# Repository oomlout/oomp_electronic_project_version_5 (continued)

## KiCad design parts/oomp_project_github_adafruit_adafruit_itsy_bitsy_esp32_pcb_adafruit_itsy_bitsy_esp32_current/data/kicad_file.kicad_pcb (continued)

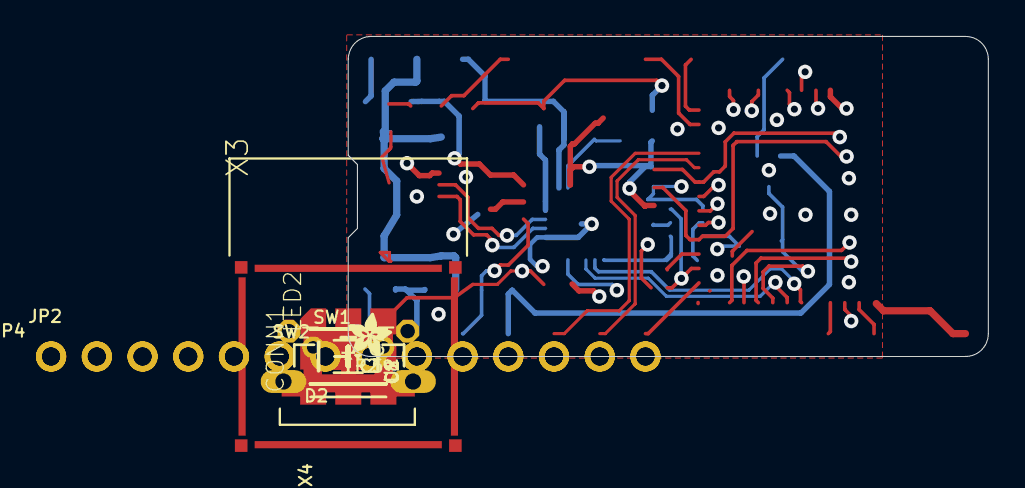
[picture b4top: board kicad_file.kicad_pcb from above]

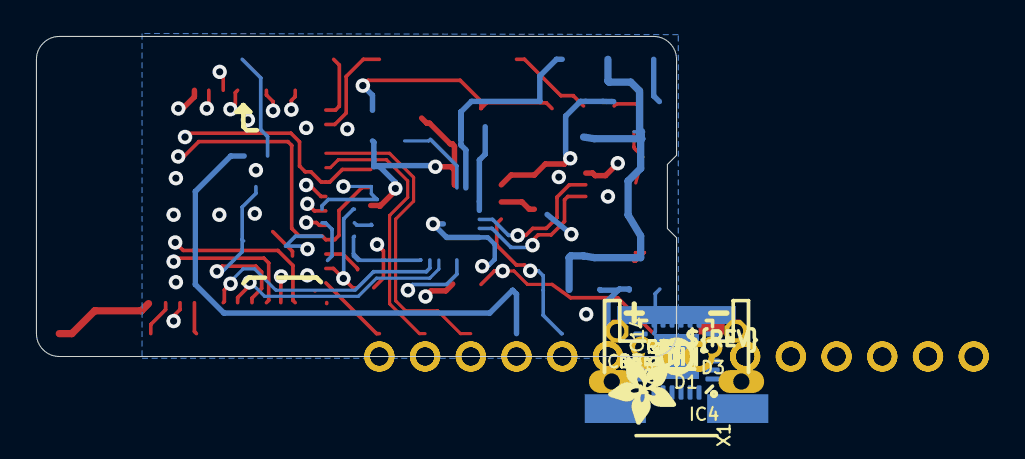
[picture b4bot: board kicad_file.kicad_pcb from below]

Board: 4 copper layers, 35.6 x 17.8 mm, 87 parts (48 on the bottom side), 42 nets.

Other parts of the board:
E$1: ADAFRUIT_2.5MM
E$2: ADAFRUIT_3.5MM
PLABEL0: PLABEL0
PLABEL1: PLABEL1
PLABEL2: PLABEL2
PLABEL3: PLABEL3
PLABEL4: PLABEL4
PLABEL5: PLABEL5
PLABEL6: PLABEL6
PLABEL7: PLABEL7
PLABEL8: PLABEL8
PLABEL9: PLABEL9
PLABEL10: PLABEL10
PLABEL11: PLABEL11
PLABEL12: PLABEL12
PLABEL13: PLABEL13
PLABEL14: PLABEL14
PLABEL15: PLABEL15
PLABEL16: PLABEL16
PLABEL17: PLABEL17
PLABEL18: PLABEL18
PLABEL19: PLABEL19
PLABEL20: PLABEL20
PLABEL21: PLABEL21
PLABEL22: PLABEL22
PLABEL23: PLABEL23
PLABEL24: PLABEL24
PLABEL25: PLABEL25
PLABEL26: PLABEL26
PLABEL27: PLABEL27
PLABEL28: PLABEL28
PLABEL29: PLABEL29
PLABEL30: PLABEL30
PLABEL31: PLABEL31
PLABEL32: PLABEL32
PLABEL33: PLABEL33
PLABEL34: PLABEL34
PLABEL35: PLABEL35
PLABEL36: PLABEL36
PLABEL37: PLABEL37
PLABEL38: PLABEL38
PLABEL39: PLABEL39
PLABEL40: PLABEL40
PLABEL41: PLABEL41
PLABEL42: PLABEL42
PLABEL43: PLABEL43
PLABEL44: PLABEL44
U$16: PCBFEAT-REV-040

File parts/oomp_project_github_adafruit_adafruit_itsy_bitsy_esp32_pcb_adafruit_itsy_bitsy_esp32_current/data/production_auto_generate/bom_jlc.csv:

Comment,Designator,Footprint,LCSC Part #
,"JP2,JP4",Adafruit ItsyBitsy ESP32-import-fps:1X14_ROUND70,C2905490
,E$1,Adafruit ItsyBitsy ESP32-import-fps:ADAFRUIT_2.5MM,
,E$2,Adafruit ItsyBitsy ESP32-import-fps:ADAFRUIT_3.5MM,
,U$16,Adafruit ItsyBitsy ESP32-import-fps:PCBFEAT-REV-040,
,PLABEL0,Adafruit ItsyBitsy ESP32-import-fps:PLABEL0,
,PLABEL1,Adafruit ItsyBitsy ESP32-import-fps:PLABEL1,
,PLABEL10,Adafruit ItsyBitsy ESP32-import-fps:PLABEL10,
,PLABEL11,Adafruit ItsyBitsy ESP32-import-fps:PLABEL11,
,PLABEL12,Adafruit ItsyBitsy ESP32-import-fps:PLABEL12,
,PLABEL13,Adafruit ItsyBitsy ESP32-import-fps:PLABEL13,
,PLABEL14,Adafruit ItsyBitsy ESP32-import-fps:PLABEL14,
,PLABEL15,Adafruit ItsyBitsy ESP32-import-fps:PLABEL15,
,PLABEL16,Adafruit ItsyBitsy ESP32-import-fps:PLABEL16,
,PLABEL17,Adafruit ItsyBitsy ESP32-import-fps:PLABEL17,
,PLABEL18,Adafruit ItsyBitsy ESP32-import-fps:PLABEL18,
,PLABEL19,Adafruit ItsyBitsy ESP32-import-fps:PLABEL19,
,PLABEL2,Adafruit ItsyBitsy ESP32-import-fps:PLABEL2,
,PLABEL20,Adafruit ItsyBitsy ESP32-import-fps:PLABEL20,
,PLABEL21,Adafruit ItsyBitsy ESP32-import-fps:PLABEL21,
,PLABEL22,Adafruit ItsyBitsy ESP32-import-fps:PLABEL22,
,PLABEL23,Adafruit ItsyBitsy ESP32-import-fps:PLABEL23,
,PLABEL24,Adafruit ItsyBitsy ESP32-import-fps:PLABEL24,
,PLABEL25,Adafruit ItsyBitsy ESP32-import-fps:PLABEL25,
,PLABEL26,Adafruit ItsyBitsy ESP32-import-fps:PLABEL26,
,PLABEL27,Adafruit ItsyBitsy ESP32-import-fps:PLABEL27,
,PLABEL28,Adafruit ItsyBitsy ESP32-import-fps:PLABEL28,
,PLABEL29,Adafruit ItsyBitsy ESP32-import-fps:PLABEL29,
,PLABEL3,Adafruit ItsyBitsy ESP32-import-fps:PLABEL3,
,PLABEL30,Adafruit ItsyBitsy ESP32-import-fps:PLABEL30,
,PLABEL31,Adafruit ItsyBitsy ESP32-import-fps:PLABEL31,
,PLABEL32,Adafruit ItsyBitsy ESP32-import-fps:PLABEL32,
,PLABEL33,Adafruit ItsyBitsy ESP32-import-fps:PLABEL33,
,PLABEL34,Adafruit ItsyBitsy ESP32-import-fps:PLABEL34,
,PLABEL35,Adafruit ItsyBitsy ESP32-import-fps:PLABEL35,
,PLABEL36,Adafruit ItsyBitsy ESP32-import-fps:PLABEL36,
,PLABEL37,Adafruit ItsyBitsy ESP32-import-fps:PLABEL37,
,PLABEL38,Adafruit ItsyBitsy ESP32-import-fps:PLABEL38,
,PLABEL39,Adafruit ItsyBitsy ESP32-import-fps:PLABEL39,
,PLABEL4,Adafruit ItsyBitsy ESP32-import-fps:PLABEL4,
,PLABEL40,Adafruit ItsyBitsy ESP32-import-fps:PLABEL40,
,PLABEL41,Adafruit ItsyBitsy ESP32-import-fps:PLABEL41,
,PLABEL42,Adafruit ItsyBitsy ESP32-import-fps:PLABEL42,
,PLABEL43,Adafruit ItsyBitsy ESP32-import-fps:PLABEL43,
,PLABEL44,Adafruit ItsyBitsy ESP32-import-fps:PLABEL44,
,PLABEL5,Adafruit ItsyBitsy ESP32-import-fps:PLABEL5,
,PLABEL6,Adafruit ItsyBitsy ESP32-import-fps:PLABEL6,
,PLABEL7,Adafruit ItsyBitsy ESP32-import-fps:PLABEL7,
,PLABEL8,Adafruit ItsyBitsy ESP32-import-fps:PLABEL8,
,PLABEL9,Adafruit ItsyBitsy ESP32-import-fps:PLABEL9,
0.1uF,"C15,C22",Adafruit ItsyBitsy ESP32-import-fps:0603-NO,C14663
10K,"R1,R2,R4,R6,R7,R8",Adafruit ItsyBitsy ESP32-import-fps:0603-NO,C98220
10uF,"C1,C5,C7,C8",Adafruit ItsyBitsy ESP32-import-fps:0805-NO,
1uF,"C3,C4,C10,C14",Adafruit ItsyBitsy ESP32-import-fps:0603-NO,C5673
20329,X4,Adafruit ItsyBitsy ESP32-import-fps:4UCONN_20329_SLIM,
20K,R5,Adafruit ItsyBitsy ESP32-import-fps:0603-NO,
47K,"R3,R9",Adafruit ItsyBitsy ESP32-import-fps:0603-NO,C2907042
74AHCT1G125DCKR,IC1,Adafruit ItsyBitsy ESP32-import-fps:SC70-5,
BAT20J,"D1,D3",Adafruit ItsyBitsy ESP32-import-fps:SOD-323,
CH9102F,IC4,Adafruit ItsyBitsy ESP32-import-fps:QFN24_4MM_SMSC,
DNP,X1,Adafruit ItsyBitsy ESP32-import-fps:JSTPH2_BATT,
DUAL NPN,Q5,Adafruit ItsyBitsy ESP32-import-fps:SOT363,
ESP32-PICO-MINI-02MINI,X3,Adafruit ItsyBitsy ESP32-import-fps:ESP32-PICO-MINI,
KMR2,"SW1,SW2",Adafruit ItsyBitsy ESP32-import-fps:BTN_RKB2_4.6X2.8,
RED,D2,Adafruit ItsyBitsy ESP32-import-fps:CHIPLED_0603_NOOUTLINE,
RT9080-3.3,U2,Adafruit ItsyBitsy ESP32-import-fps:SOT23-5,
STEMMA_I2C_QTRA,CONN1,Adafruit ItsyBitsy ESP32-import-fps:JST_SH4_RA,
WS2812B_SK6805_1515,LED2,Adafruit ItsyBitsy ESP32-import-fps:SK6805_1515,
